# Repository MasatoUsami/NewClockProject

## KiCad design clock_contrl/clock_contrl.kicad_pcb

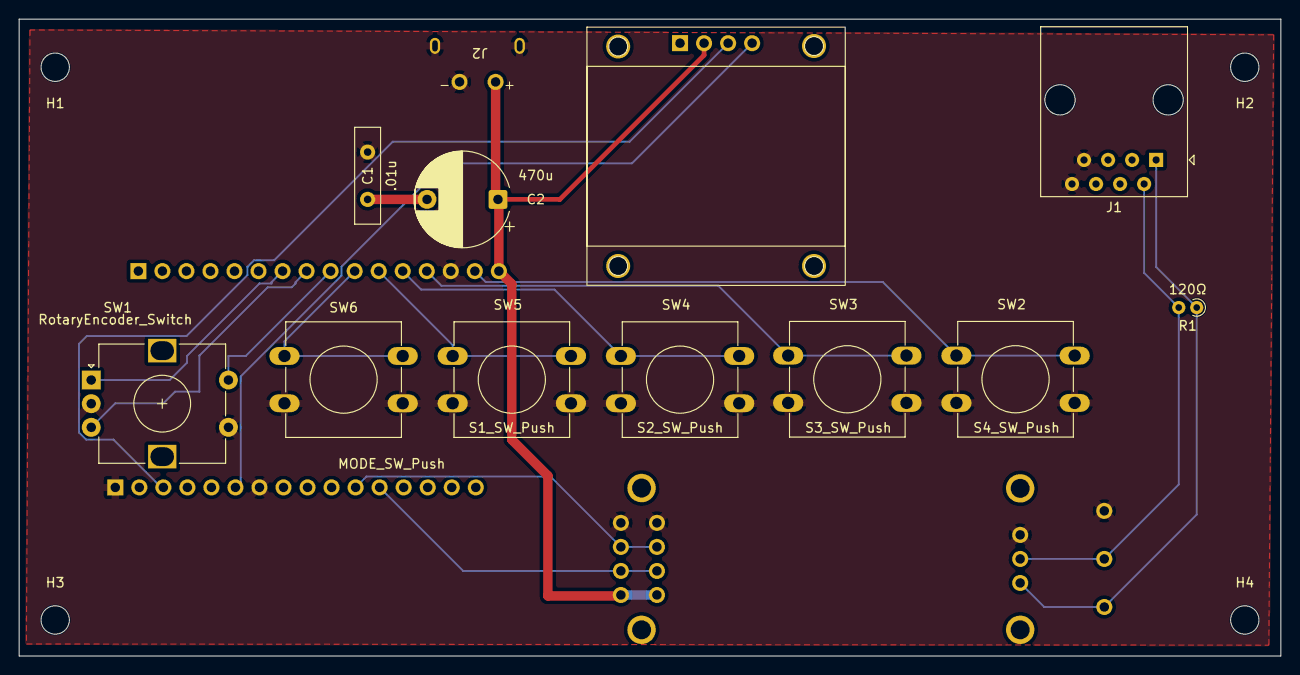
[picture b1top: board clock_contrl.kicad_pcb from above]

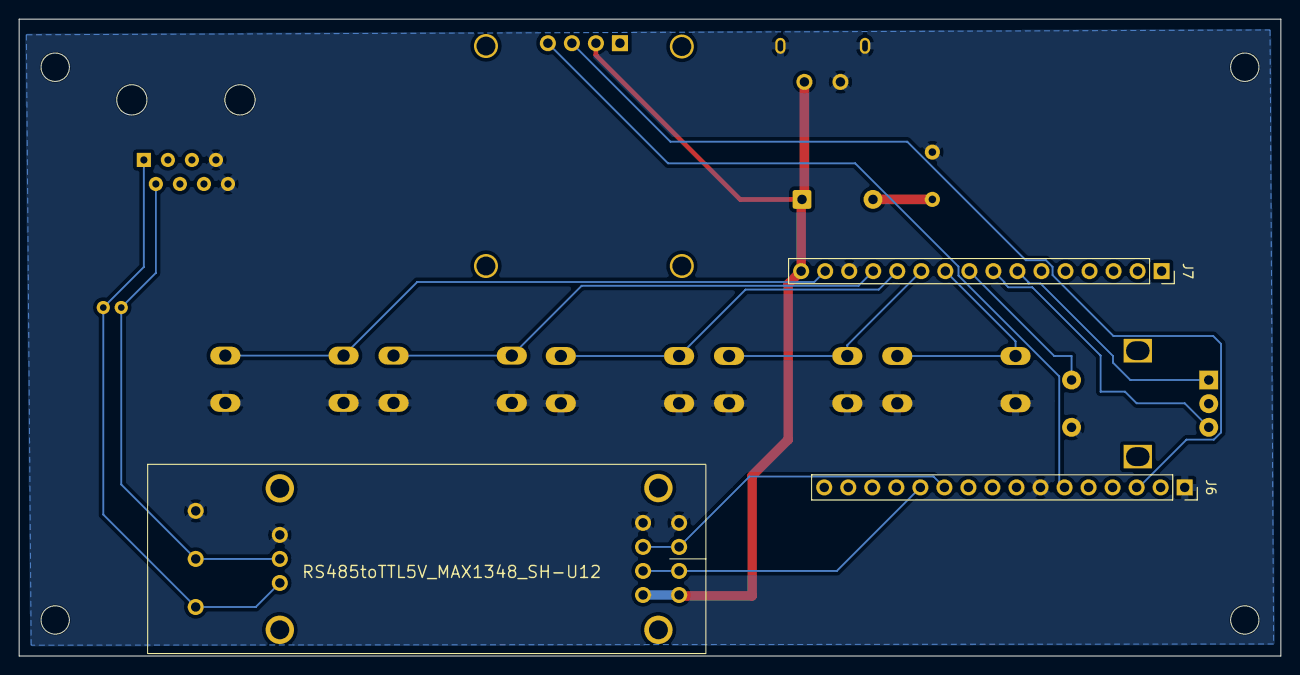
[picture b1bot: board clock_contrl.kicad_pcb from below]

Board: 2 copper layers, 133.4 x 67.3 mm, 20 parts (3 on the bottom side), 17 nets.

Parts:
C1: .01u; C_Disc_D10.0mm_W2.5mm_P5.00mm
C2: 470u; CP_Radial_D10.0mm_P7.50mm
H1, H2, H3, H4: MountingHole; MountingHole_3mm
J1: RJ45; RJ45_Amphenol_54602-x08_Horizontal
J2: USB_C_Receptacle_PowerOnly_6P; USB_C_Receptacle_GCT_USB4125-xx-x-0190_6P_TopMnt_Horizontal
J6: Conn_01x16_Socket; PinSocket_1x16_P2.54mm_Vertical
J7: Conn_01x08_Socket; PinSocket_1x16_P2.54mm_Vertical
R1: 120Ω; R_Axial_DIN0204_L3.6mm_D1.6mm_P1.90mm_Vertical
RS485toTTL5V_MAX1348_SH-U12: f00c1b2a-24ff-4943-b02c-ccbf93357c9b
RS485toTTL5V_MAX1348_SH-U12#2: d20c897a-e8f7-4042-81bd-1f98a1eacd4c
SW1: RotaryEncoder_Switch; RotaryEncoder_Alps_EC12E-Switch_Vertical_H20mm
SW2: S4_SW_Push; SW_PUSH-12mm
SW3: S3_SW_Push; SW_PUSH-12mm
SW4: S2_SW_Push; SW_PUSH-12mm
SW5: S1_SW_Push; SW_PUSH-12mm
SW6: MODE_SW_Push; SW_PUSH-12mm
U4: OLED_SSD1306_128x32_I2C; Adafruit_SSD1306_I2c

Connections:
/Net-(J7-Pin_12): J7.12, SW3.1
/Net-(J7-Pin_13): J7.13, SW2.1
/Net-(J7-Pin_14): J7.14, SW4.1
/Net-(J7-Pin_26): J7.26, SW6.1
/Net-(J7-Pin_27): J7.27, SW5.1
/Net-(J7-Pin_32): J7.32, SW1.A
/Net-(J7-Pin_33): J7.33, SW1.B
/Net-(J7_Pin_25): J7.25, SW1.S1
GND: C1.2, J1.7, J1.8, J2.5, J2.SH (SHIELD_SH), J6.GND, J7.GND, RS485toTTL5V_MAX1348_SH-U12#2.GND, SW1.C, SW1.S2, SW2.2, SW3.2, SW4.2, SW5.2, SW6.2
unnamed: C1.1, C2.2
unnamed: J1.1, R1.1, RS485toTTL5V_MAX1348_SH-U12#2.A+
unnamed: J1.2, R1.2, RS485toTTL5V_MAX1348_SH-U12#2.B-
unnamed: J6.16, RS485toTTL5V_MAX1348_SH-U12#2.TXD
unnamed: J6.17, RS485toTTL5V_MAX1348_SH-U12#2.RXD
unnamed: J6.21, U4.SDA
unnamed: J6.22, U4.SCL
unnamed: C2.1, J2.6, J7.5V, RS485toTTL5V_MAX1348_SH-U12#2.5VO, U4.VCC

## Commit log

2026-05-05 @柱時計を自由に駆動させるプロジェクトです。現在コントロールパネルの基盤作り中です。@
2026-05-06 部品の配置を変えてみました
2026-05-11 コントロールボックスの基盤を完成しました
2026-05-20 基盤のUSB端子とRJ45端子を実際のフットプリントに変更しました。
